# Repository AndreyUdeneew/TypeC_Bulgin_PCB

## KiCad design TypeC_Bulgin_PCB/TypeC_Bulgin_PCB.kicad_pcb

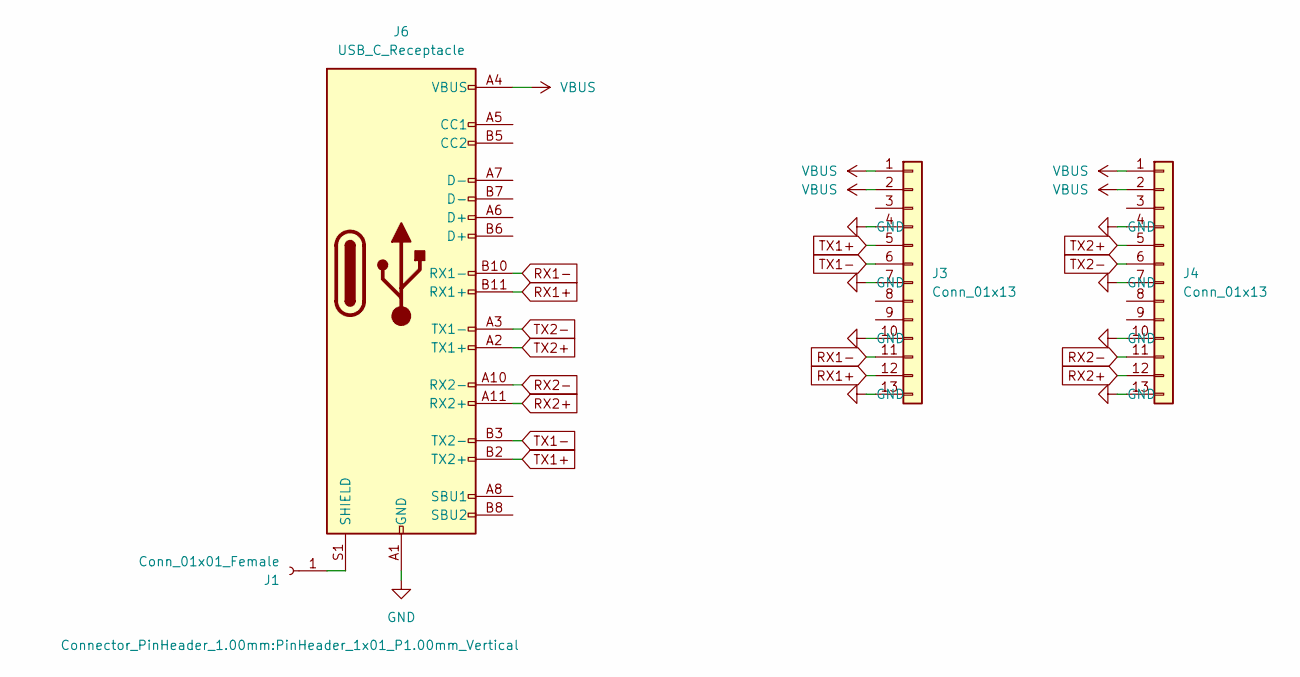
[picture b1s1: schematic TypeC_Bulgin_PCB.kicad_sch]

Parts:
J1: Conn_01x01_Female; PinHeader_1x01_P1.00mm_Vertical
J3, J4: Conn_01x13; ADT_13pin
J6: USB_C_Receptacle; USB_C_Receptacle_JAE_DX07S024WJ3R400

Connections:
GND: J3.4, J3.7, J3.10, J3.13, J4.4, J4.7, J4.10, J4.13, J6.A1 (GND), J6.A12 (GND), J6.B1 (GND), J6.B12 (GND)
unnamed: J1.1, J6.S1 (SHIELD)
RX1+: J3.12, J6.B11 (RX1+)
RX1-: J3.11, J6.B10 (RX1-)
RX2+: J4.12, J6.A11 (RX2+)
RX2-: J4.11, J6.A10 (RX2-)
TX1+: J3.5, J6.B2 (TX2+)
TX1-: J3.6, J6.B3 (TX2-)
TX2+: J4.5, J6.A2 (TX1+)
TX2-: J4.6, J6.A3 (TX1-)
VBUS: J3.1, J3.2, J4.1, J4.2, J6.A4 (VBUS), J6.A9 (VBUS), J6.B4 (VBUS), J6.B9 (VBUS)

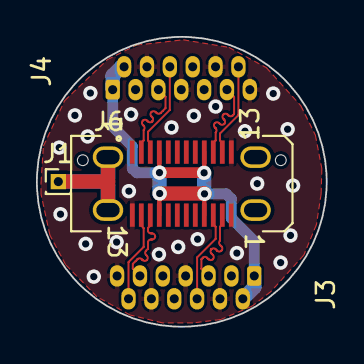
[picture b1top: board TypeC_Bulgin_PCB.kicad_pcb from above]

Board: 2 copper layers, 16.1 x 16.1 mm, 4 parts (0 on the bottom side), 11 nets.

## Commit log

2022-05-13 v0.1 PCB prototype was created
2022-05-13 v0.2 some changes
2022-05-14 v0.3 DRC has been changed
2022-05-14 v0.31 DRC was corrected
2022-05-15 v0.4 round shape was created
2022-05-16 v0.5 real size was applied
2022-05-16 v0.6 connectors prototype were added
2022-05-16 v0.7 13 pin connectors were added
2022-05-17 v0.8 ADT 13 pins was created
2022-05-19 v0.9 Land patterns were corrected
2022-05-21 v0.91 circuit was corrected
2022-05-24 v0.92 land patterns of ADT13pins were corrected
2022-05-26 Auto stash before merge of "main" and "origin/main"
2022-05-27 v0.93 differential pairs were routed and equalised, polydons were placed
2022-05-27 v0.94 Gerbers wwre created
2022-05-27 v0.95 DRC errors were corrected
2022-05-27 v0.96 errors were corrected
2022-06-03 v0.97 gerbers of mask were added
